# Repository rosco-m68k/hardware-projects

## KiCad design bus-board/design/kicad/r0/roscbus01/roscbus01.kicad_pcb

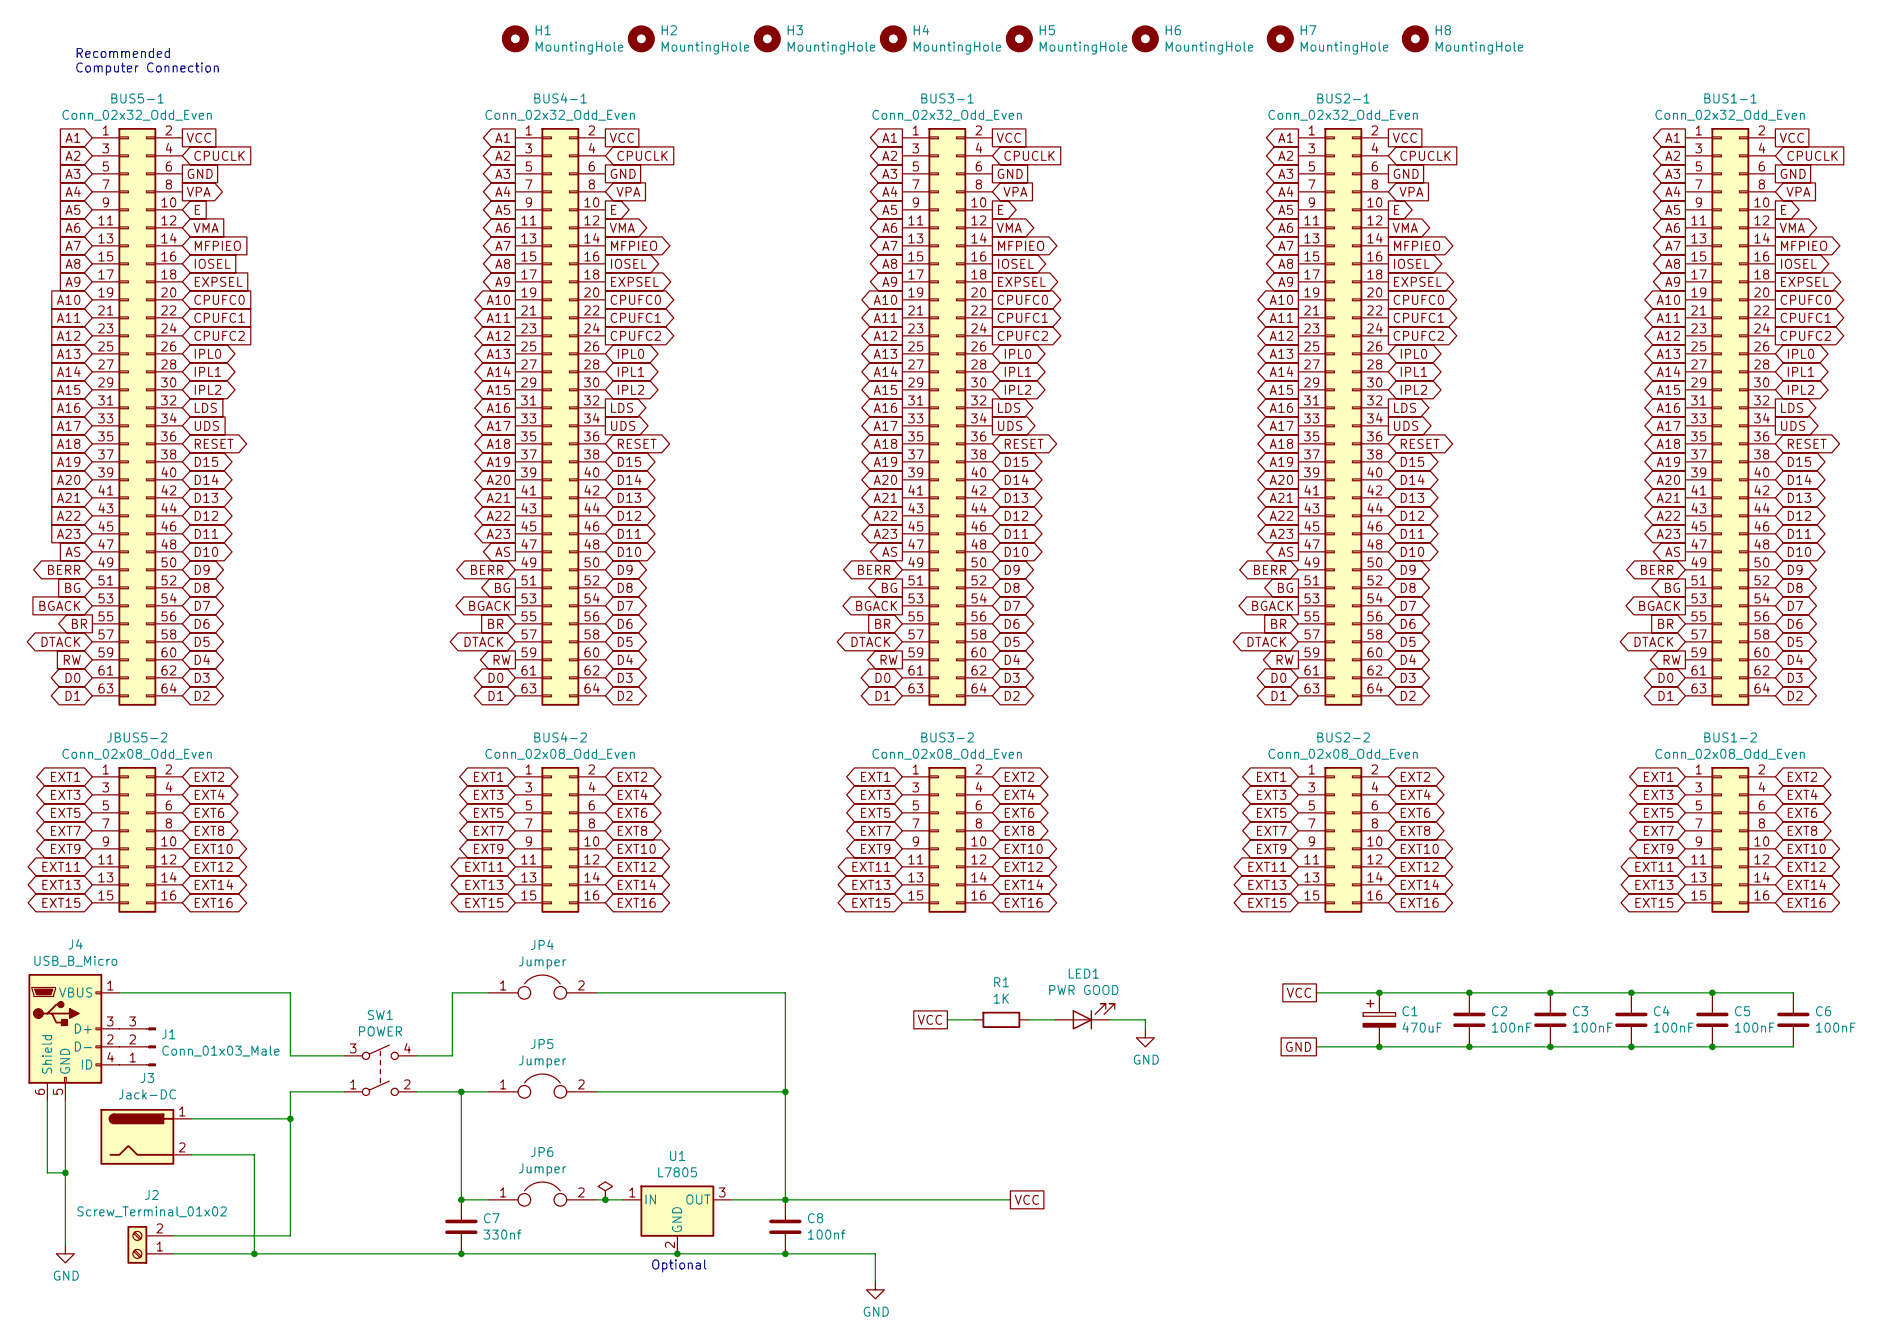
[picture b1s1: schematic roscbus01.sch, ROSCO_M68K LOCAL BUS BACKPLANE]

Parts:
BUS1-1, BUS2-1, BUS3-1, BUS4-1, BUS5-1: Conn_02x32_Odd_Even; pin-2X32
BUS1-2, BUS2-2, BUS3-2, BUS4-2: Conn_02x08_Odd_Even; pin-2X8
C1: 470uF; C-Electrolytic-3,5-10
C2, C3, C4, C5, C6: 100nF; C_Rect_L7.0mm_W2.0mm_P5.00mm
C7: 330nf; C_Rect_L7.0mm_W2.0mm_P5.00mm
C8: 100nf; C_Rect_L7.0mm_W2.0mm_P5.00mm
H1, H2, H3, H4, H5, H6, H7, H8: MountingHole; MountingHole_3.2mm_M3
J1: Conn_01x03_Male; PinHeader_1x03_P2.54mm_Vertical
J2: Screw_Terminal_01x02; TerminalBlock_Phoenix_MPT-0,5-2-2.54_1x02_P2.54mm_Horizontal
J3: Jack-DC; BarrelJack_Wuerth_6941xx301002
J4: USB_B_Micro; USB_Micro-B_Wuerth_614105150721_Vertical
JBUS5-2: Conn_02x08_Odd_Even; pin-2X8
JP4, JP5, JP6: Jumper; PinHeader_1x02_P2.54mm_Vertical
LED1: PWR GOOD; LED_D5.0mm
R1: 1K; R-0207_10
SW1: POWER; NKK-M2021SS1W01
U1: L7805; TO-220F-3_Horizontal_TabDown

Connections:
A1: BUS1-1.1, BUS2-1.1, BUS3-1.1, BUS4-1.1, BUS5-1.1
A2: BUS1-1.3, BUS2-1.3, BUS3-1.3, BUS4-1.3, BUS5-1.3
A3: BUS1-1.5, BUS2-1.5, BUS3-1.5, BUS4-1.5, BUS5-1.5
A4: BUS1-1.7, BUS2-1.7, BUS3-1.7, BUS4-1.7, BUS5-1.7
A5: BUS1-1.9, BUS2-1.9, BUS3-1.9, BUS4-1.9, BUS5-1.9
A6: BUS1-1.11, BUS2-1.11, BUS3-1.11, BUS4-1.11, BUS5-1.11
A7: BUS1-1.13, BUS2-1.13, BUS3-1.13, BUS4-1.13, BUS5-1.13
A8: BUS1-1.15, BUS2-1.15, BUS3-1.15, BUS4-1.15, BUS5-1.15
A9: BUS1-1.17, BUS2-1.17, BUS3-1.17, BUS4-1.17, BUS5-1.17
A10: BUS1-1.19, BUS2-1.19, BUS3-1.19, BUS4-1.19, BUS5-1.19
A11: BUS1-1.21, BUS2-1.21, BUS3-1.21, BUS4-1.21, BUS5-1.21
A12: BUS1-1.23, BUS2-1.23, BUS3-1.23, BUS4-1.23, BUS5-1.23
A13: BUS1-1.25, BUS2-1.25, BUS3-1.25, BUS4-1.25, BUS5-1.25
A14: BUS1-1.27, BUS2-1.27, BUS3-1.27, BUS4-1.27, BUS5-1.27
A15: BUS1-1.29, BUS2-1.29, BUS3-1.29, BUS4-1.29, BUS5-1.29
A16: BUS1-1.31, BUS2-1.31, BUS3-1.31, BUS4-1.31, BUS5-1.31
A17: BUS1-1.33, BUS2-1.33, BUS3-1.33, BUS4-1.33, BUS5-1.33
A18: BUS1-1.35, BUS2-1.35, BUS3-1.35, BUS4-1.35, BUS5-1.35
A19: BUS1-1.37, BUS2-1.37, BUS3-1.37, BUS4-1.37, BUS5-1.37
A20: BUS1-1.39, BUS2-1.39, BUS3-1.39, BUS4-1.39, BUS5-1.39
A21: BUS1-1.41, BUS2-1.41, BUS3-1.41, BUS4-1.41, BUS5-1.41
A22: BUS1-1.43, BUS2-1.43, BUS3-1.43, BUS4-1.43, BUS5-1.43
A23: BUS1-1.45, BUS2-1.45, BUS3-1.45, BUS4-1.45, BUS5-1.45
AS: BUS1-1.47, BUS2-1.47, BUS3-1.47, BUS4-1.47, BUS5-1.47
BERR: BUS1-1.49, BUS2-1.49, BUS3-1.49, BUS4-1.49, BUS5-1.49
BG: BUS1-1.51, BUS2-1.51, BUS3-1.51, BUS4-1.51, BUS5-1.51
BGACK: BUS1-1.53, BUS2-1.53, BUS3-1.53, BUS4-1.53, BUS5-1.53
BR: BUS1-1.55, BUS2-1.55, BUS3-1.55, BUS4-1.55, BUS5-1.55
CPUCLK: BUS1-1.4, BUS2-1.4, BUS3-1.4, BUS4-1.4, BUS5-1.4
CPUFC0: BUS1-1.20, BUS2-1.20, BUS3-1.20, BUS4-1.20, BUS5-1.20
CPUFC1: BUS1-1.22, BUS2-1.22, BUS3-1.22, BUS4-1.22, BUS5-1.22
CPUFC2: BUS1-1.24, BUS2-1.24, BUS3-1.24, BUS4-1.24, BUS5-1.24
D0: BUS1-1.61, BUS2-1.61, BUS3-1.61, BUS4-1.61, BUS5-1.61
D1: BUS1-1.63, BUS2-1.63, BUS3-1.63, BUS4-1.63, BUS5-1.63
D2: BUS1-1.64, BUS2-1.64, BUS3-1.64, BUS4-1.64, BUS5-1.64
D3: BUS1-1.62, BUS2-1.62, BUS3-1.62, BUS4-1.62, BUS5-1.62
D4: BUS1-1.60, BUS2-1.60, BUS3-1.60, BUS4-1.60, BUS5-1.60
D5: BUS1-1.58, BUS2-1.58, BUS3-1.58, BUS4-1.58, BUS5-1.58
D6: BUS1-1.56, BUS2-1.56, BUS3-1.56, BUS4-1.56, BUS5-1.56
D7: BUS1-1.54, BUS2-1.54, BUS3-1.54, BUS4-1.54, BUS5-1.54
D8: BUS1-1.52, BUS2-1.52, BUS3-1.52, BUS4-1.52, BUS5-1.52
D9: BUS1-1.50, BUS2-1.50, BUS3-1.50, BUS4-1.50, BUS5-1.50
D10: BUS1-1.48, BUS2-1.48, BUS3-1.48, BUS4-1.48, BUS5-1.48
D11: BUS1-1.46, BUS2-1.46, BUS3-1.46, BUS4-1.46, BUS5-1.46
D12: BUS1-1.44, BUS2-1.44, BUS3-1.44, BUS4-1.44, BUS5-1.44
D13: BUS1-1.42, BUS2-1.42, BUS3-1.42, BUS4-1.42, BUS5-1.42
D14: BUS1-1.40, BUS2-1.40, BUS3-1.40, BUS4-1.40, BUS5-1.40
D15: BUS1-1.38, BUS2-1.38, BUS3-1.38, BUS4-1.38, BUS5-1.38
DTACK: BUS1-1.57, BUS2-1.57, BUS3-1.57, BUS4-1.57, BUS5-1.57
E: BUS1-1.10, BUS2-1.10, BUS3-1.10, BUS4-1.10, BUS5-1.10
EXPSEL: BUS1-1.18, BUS2-1.18, BUS3-1.18, BUS4-1.18, BUS5-1.18
EXT1: BUS1-2.1, BUS2-2.1, BUS3-2.1, BUS4-2.1, JBUS5-2.1
EXT2: BUS1-2.2, BUS2-2.2, BUS3-2.2, BUS4-2.2, JBUS5-2.2
EXT3: BUS1-2.3, BUS2-2.3, BUS3-2.3, BUS4-2.3, JBUS5-2.3
EXT4: BUS1-2.4, BUS2-2.4, BUS3-2.4, BUS4-2.4, JBUS5-2.4
EXT5: BUS1-2.5, BUS2-2.5, BUS3-2.5, BUS4-2.5, JBUS5-2.5
EXT6: BUS1-2.6, BUS2-2.6, BUS3-2.6, BUS4-2.6, JBUS5-2.6
EXT7: BUS1-2.7, BUS2-2.7, BUS3-2.7, BUS4-2.7, JBUS5-2.7
EXT8: BUS1-2.8, BUS2-2.8, BUS3-2.8, BUS4-2.8, JBUS5-2.8
EXT9: BUS1-2.9, BUS2-2.9, BUS3-2.9, BUS4-2.9, JBUS5-2.9
EXT10: BUS1-2.10, BUS2-2.10, BUS3-2.10, BUS4-2.10, JBUS5-2.10
EXT11: BUS1-2.11, BUS2-2.11, BUS3-2.11, BUS4-2.11, JBUS5-2.11
EXT12: BUS1-2.12, BUS2-2.12, BUS3-2.12, BUS4-2.12, JBUS5-2.12
EXT13: BUS1-2.13, BUS2-2.13, BUS3-2.13, BUS4-2.13, JBUS5-2.13
EXT14: BUS1-2.14, BUS2-2.14, BUS3-2.14, BUS4-2.14, JBUS5-2.14
EXT15: BUS1-2.15, BUS2-2.15, BUS3-2.15, BUS4-2.15, JBUS5-2.15
EXT16: BUS1-2.16, BUS2-2.16, BUS3-2.16, BUS4-2.16, JBUS5-2.16
GND: BUS1-1.6, BUS2-1.6, BUS3-1.6, BUS4-1.6, BUS5-1.6, C1.2, C2.2, C3.2, C4.2, C5.2, C6.2, C7.2, C8.2, J2.1, J3.2, J4.5 (GND), J4.6 (Shield), LED1.1 (K), U1.2 (GND)
IOSEL: BUS1-1.16, BUS2-1.16, BUS3-1.16, BUS4-1.16, BUS5-1.16
IPL0: BUS1-1.26, BUS2-1.26, BUS3-1.26, BUS4-1.26, BUS5-1.26
IPL1: BUS1-1.28, BUS2-1.28, BUS3-1.28, BUS4-1.28, BUS5-1.28
IPL2: BUS1-1.30, BUS2-1.30, BUS3-1.30, BUS4-1.30, BUS5-1.30
LDS: BUS1-1.32, BUS2-1.32, BUS3-1.32, BUS4-1.32, BUS5-1.32
MFPIEO: BUS1-1.14, BUS2-1.14, BUS3-1.14, BUS4-1.14, BUS5-1.14
unnamed: C7.1, JP5.1, JP6.1, SW1.2
unnamed: J1.1, J4.4 (ID)
unnamed: J1.2, J4.2 (D-)
unnamed: J1.3, J4.3 (D+)
unnamed: J2.2, J3.1, SW1.1
unnamed: J4.1 (VBUS), SW1.3
unnamed: JP4.1, SW1.4
unnamed: JP6.2, U1.1 (IN)
unnamed: LED1.2 (A), R1.1
RESET: BUS1-1.36, BUS2-1.36, BUS3-1.36, BUS4-1.36, BUS5-1.36
RW: BUS1-1.59, BUS2-1.59, BUS3-1.59, BUS4-1.59, BUS5-1.59
UDS: BUS1-1.34, BUS2-1.34, BUS3-1.34, BUS4-1.34, BUS5-1.34
VCC: BUS1-1.2, BUS2-1.2, BUS3-1.2, BUS4-1.2, BUS5-1.2, C1.1, C2.1, C3.1, C4.1, C5.1, C6.1, C8.1, JP4.2, JP5.2, R1.2, U1.3 (OUT)
VMA: BUS1-1.12, BUS2-1.12, BUS3-1.12, BUS4-1.12, BUS5-1.12
VPA: BUS1-1.8, BUS2-1.8, BUS3-1.8, BUS4-1.8, BUS5-1.8

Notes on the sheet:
Recommended Computer Connection
Optional

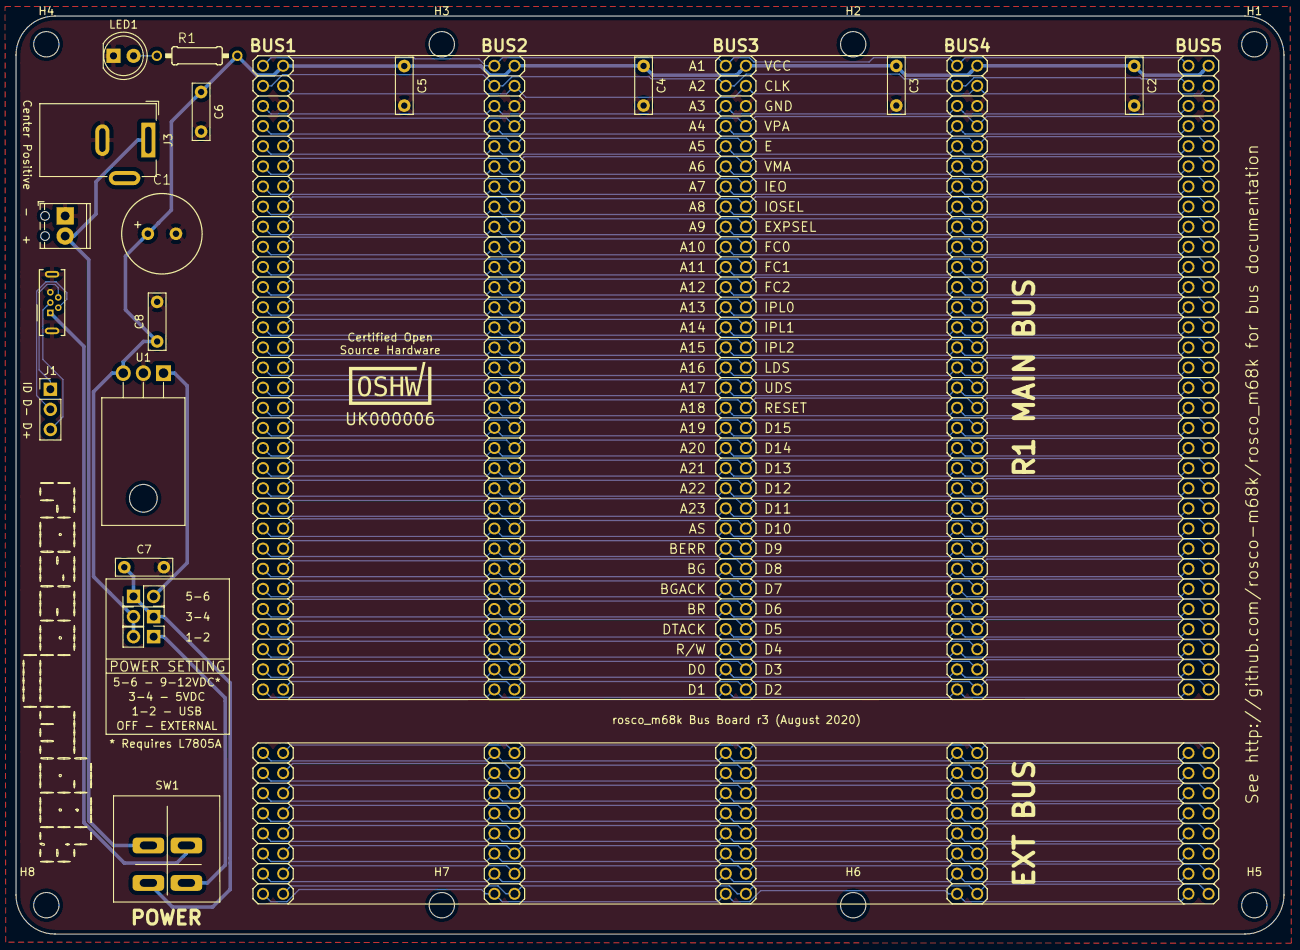
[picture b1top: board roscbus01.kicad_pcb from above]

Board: 2 copper layers, 160.1 x 115.9 mm, 38 parts (0 on the bottom side), 89 nets.

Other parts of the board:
OSHW_Mono_0.25_Scale: UK000006; OSHW_Mono_0.25_Scale

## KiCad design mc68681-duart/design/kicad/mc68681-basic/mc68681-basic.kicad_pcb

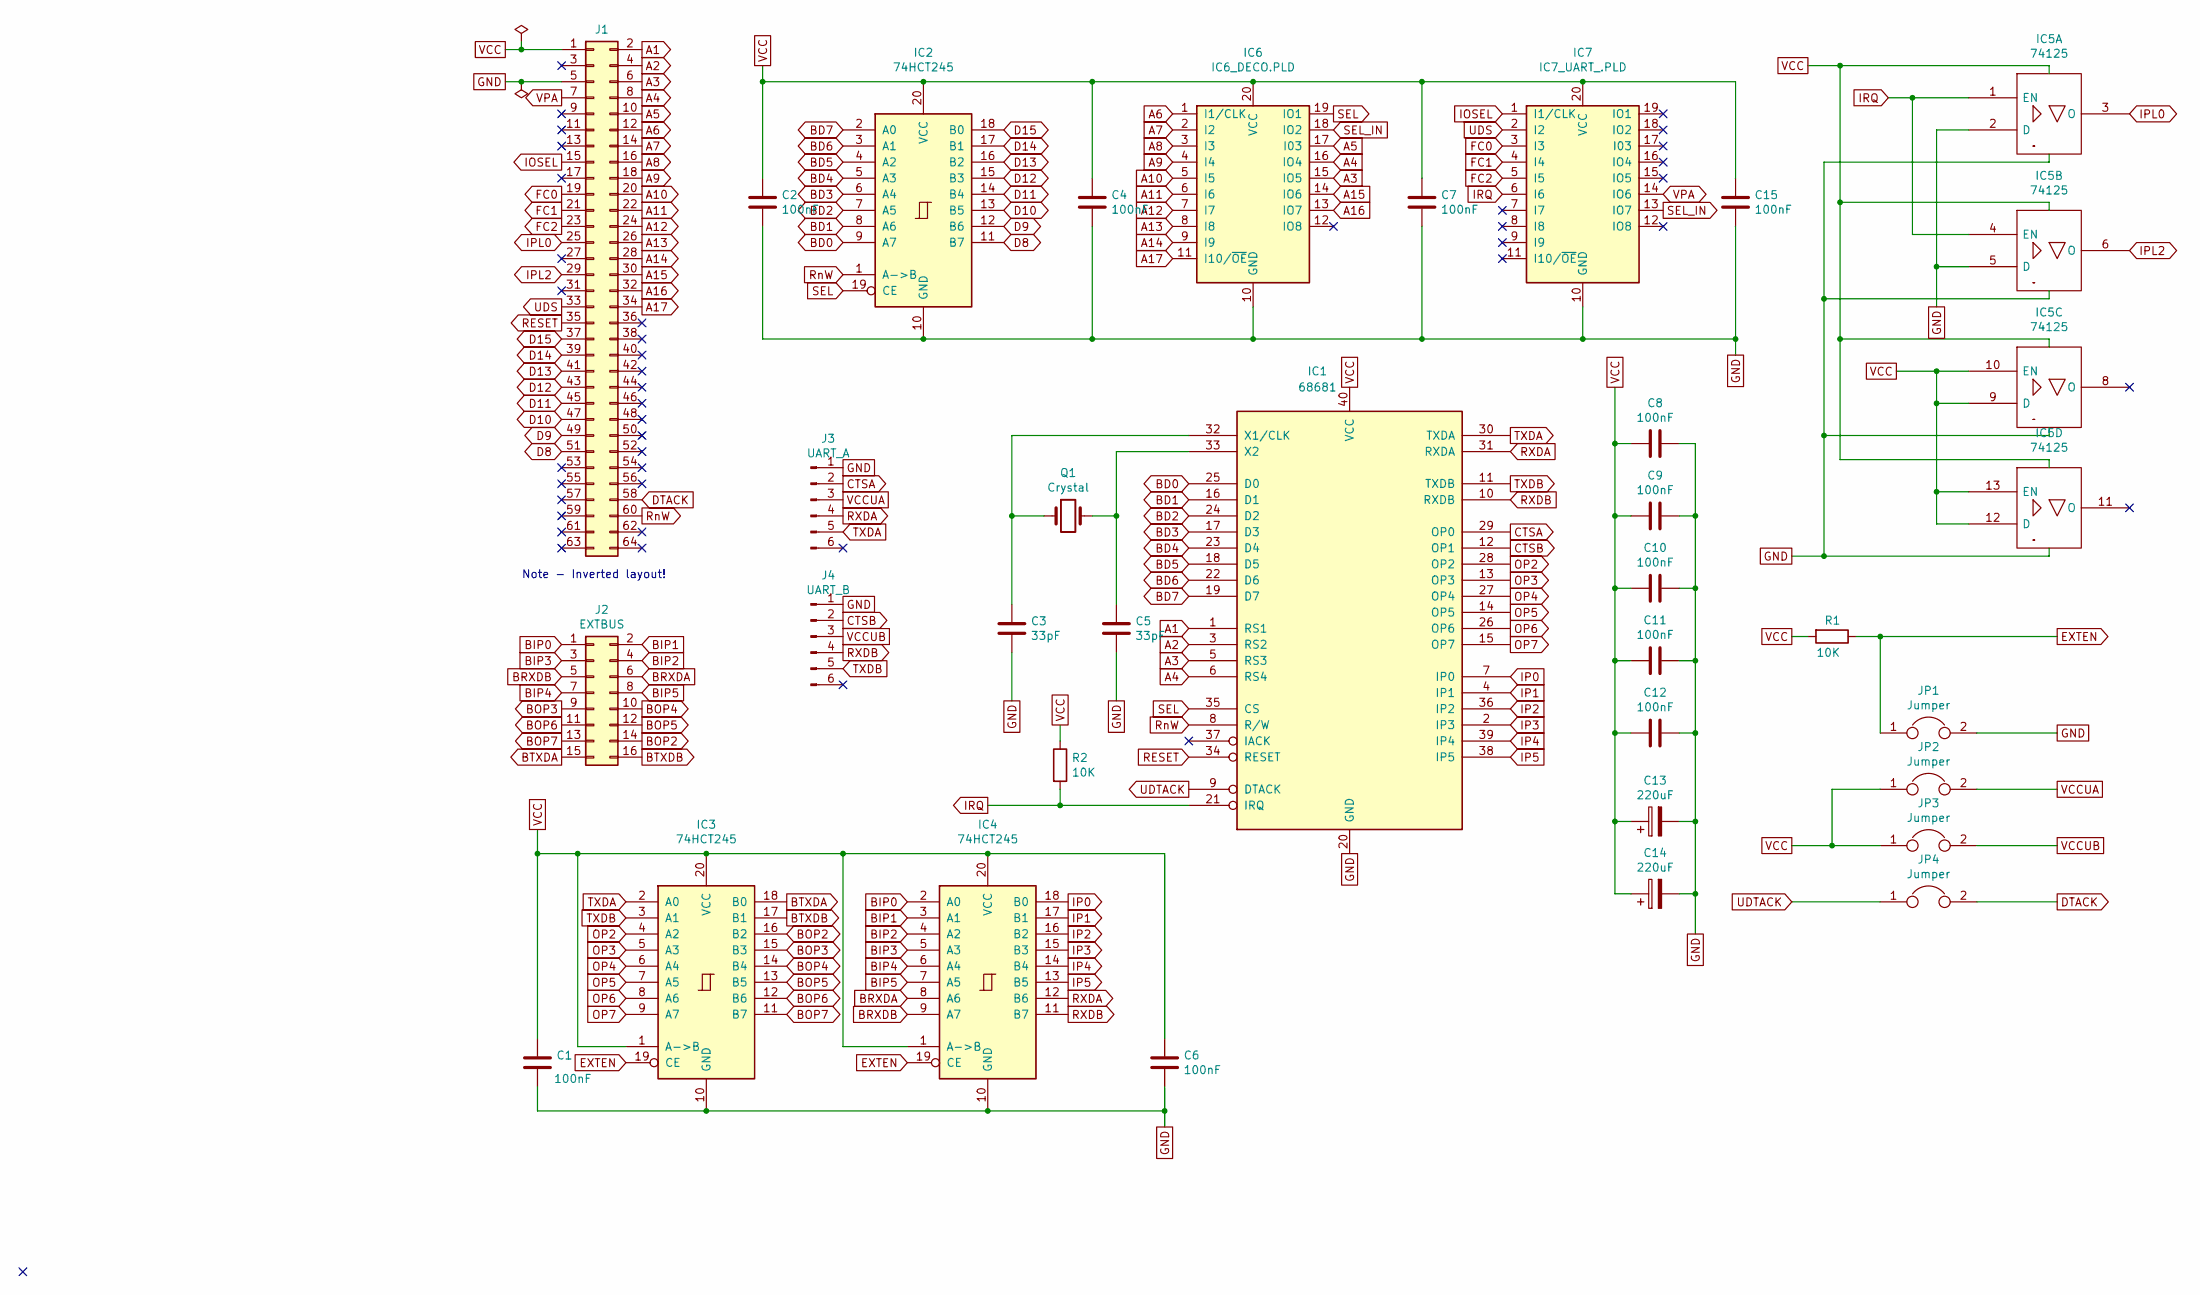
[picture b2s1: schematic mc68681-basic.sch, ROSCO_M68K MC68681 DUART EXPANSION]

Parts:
C1, C2, C4, C6, C7, C8, C9, C10, C11, C12, C15: 100nF; C2.5-3
C3, C5: 33pF; C2.5-3
C13, C14: 220uF; CP_Radial_D6.3mm_P2.50mm
IC1: 68681; DIP-40_W15.24mm_Socket_LongPads
IC2, IC3, IC4: 74HCT245; DIP-20_W7.62mm_Socket_LongPads
IC5: 74125; DIP-14_W7.62mm_Socket_LongPads
IC6: IC6_DECO.PLD; DIP-20_W7.62mm_Socket_LongPads
IC7: IC7_UART_.PLD; DIP-20_W7.62mm_Socket_LongPads
J1: Conn_02x32_Odd_Even; PinHeader_2x32_P2.54mm_Vertical
J2: EXTBUS; PinHeader_2x08_P2.54mm_Vertical
J3: UART_A; PinHeader_1x06_P2.54mm_Vertical
J4: UART_B; PinHeader_1x06_P2.54mm_Vertical
JP1, JP2, JP3, JP4: Jumper; PinHeader_1x02_P2.54mm_Vertical
Q1: Crystal; Crystal_HC49-4H_Vertical
R1, R2: 10K; R_Axial_DIN0207_L6.3mm_D2.5mm_P10.16mm_Horizontal

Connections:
A1: IC1.1 (RS1), J1.2
A2: IC1.3 (RS2), J1.4
A3: IC1.5 (RS3), IC6.15 (IO5), J1.6
A4: IC1.6 (RS4), IC6.16 (IO4), J1.8
A5: IC6.17 (I03), J1.10
A6: IC6.1 (I1/CLK), J1.12
A7: IC6.2 (I2), J1.14
A8: IC6.3 (I3), J1.16
A9: IC6.4 (I4), J1.18
A10: IC6.5 (I5), J1.20
A11: IC6.6 (I6), J1.22
A12: IC6.7 (I7), J1.24
A13: IC6.8 (I8), J1.26
A14: IC6.9 (I9), J1.28
A15: IC6.14 (IO6), J1.30
A16: IC6.13 (IO7), J1.32
A17: IC6.11 (I10/~OE~), J1.34
BD0: IC1.25 (D0), IC2.9 (A7)
BD1: IC1.16 (D1), IC2.8 (A6)
BD2: IC1.24 (D2), IC2.7 (A5)
BD3: IC1.17 (D3), IC2.6 (A4)
BD4: IC1.23 (D4), IC2.5 (A3)
BD5: IC1.18 (D5), IC2.4 (A2)
BD6: IC1.22 (D6), IC2.3 (A1)
BD7: IC1.19 (D7), IC2.2 (A0)
BIP0: IC4.2 (A0), J2.1
BIP1: IC4.3 (A1), J2.2
BIP2: IC4.4 (A2), J2.4
BIP3: IC4.5 (A3), J2.3
BIP4: IC4.6 (A4), J2.7
BIP5: IC4.7 (A5), J2.8
BOP2: IC3.16 (B2), J2.14
BOP3: IC3.15 (B3), J2.9
BOP4: IC3.14 (B4), J2.10
BOP5: IC3.13 (B5), J2.12
BOP6: IC3.12 (B6), J2.11
BOP7: IC3.11 (B7), J2.13
BRXDA: IC4.8 (A6), J2.6
BRXDB: IC4.9 (A7), J2.5
BTXDA: IC3.18 (B0), J2.15
BTXDB: IC3.17 (B1), J2.16
CTSA: IC1.29 (OP0), J3.2
CTSB: IC1.12 (OP1), J4.2
D8: IC2.11 (B7), J1.51
D9: IC2.12 (B6), J1.49
D10: IC2.13 (B5), J1.47
D11: IC2.14 (B4), J1.45
D12: IC2.15 (B3), J1.43
D13: IC2.16 (B2), J1.41
D14: IC2.17 (B1), J1.39
D15: IC2.18 (B0), J1.37
DTACK: J1.58, JP4.2
EXTEN: IC3.19 (CE), IC4.19 (CE), JP1.1, R1.1
FC0: IC7.3 (I3), J1.19
FC1: IC7.4 (I4), J1.21
FC2: IC7.5 (I5), J1.23
IOSEL: IC7.1 (I1/CLK), J1.15
IP0: IC1.7 (IP0), IC4.18 (B0)
IP1: IC1.4 (IP1), IC4.17 (B1)
IP2: IC1.36 (IP2), IC4.16 (B2)
IP3: IC1.2 (IP3), IC4.15 (B3)
IP4: IC1.39 (IP4), IC4.14 (B4)
IP5: IC1.38 (IP5), IC4.13 (B5)
IPL0: IC5.3 (O), J1.25
IPL2: IC5.6 (O), J1.29
IRQ: IC1.21 (IRQ), IC5.1 (EN), IC5.4 (EN), IC7.6 (I6), R2.2
unnamed: C3.1, IC1.32 (X1/CLK), Q1.1
unnamed: C5.1, IC1.33 (X2), Q1.2
OP2: IC1.28 (OP2), IC3.4 (A2)
OP3: IC1.13 (OP3), IC3.5 (A3)
OP4: IC1.27 (OP4), IC3.6 (A4)
OP5: IC1.14 (OP5), IC3.7 (A5)
OP6: IC1.26 (OP6), IC3.8 (A6)
OP7: IC1.15 (OP7), IC3.9 (A7)
RESET: IC1.34 (RESET), J1.35
RXDA: IC1.31 (RXDA), IC4.12 (B6), J3.4
RXDB: IC1.10 (RXDB), IC4.11 (B7), J4.4
RnW: IC1.8 (R/W), IC2.1 (A->B), J1.60
SEL: IC1.35 (CS), IC2.19 (CE), IC6.19 (IO1)
SEL_IN: IC6.18 (IO2), IC7.13 (IO7)
TXDA: IC1.30 (TXDA), IC3.2 (A0), J3.5
TXDB: IC1.11 (TXDB), IC3.3 (A1), J4.5
UDS: IC7.2 (I2), J1.33
UDTACK: IC1.9 (DTACK), JP4.1
VCCUA: J3.3, JP2.2
VCCUB: J4.3, JP3.2
VPA: IC7.14 (IO6), J1.7

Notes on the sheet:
Note - Inverted layout!

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
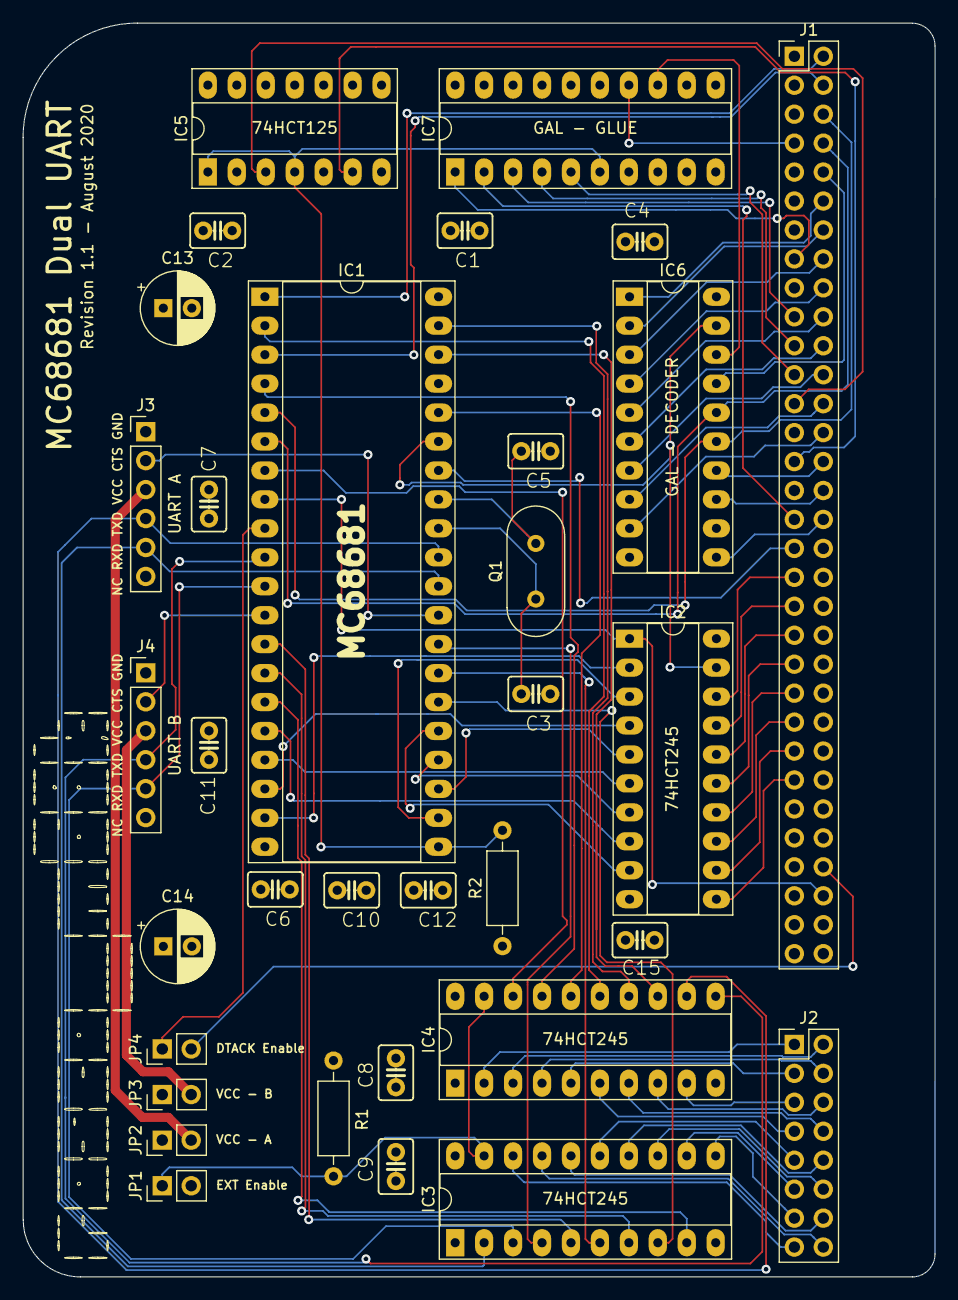
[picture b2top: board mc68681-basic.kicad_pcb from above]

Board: 4 copper layers, 80.0 x 110.0 mm, 33 parts (0 on the bottom side), 89 nets.

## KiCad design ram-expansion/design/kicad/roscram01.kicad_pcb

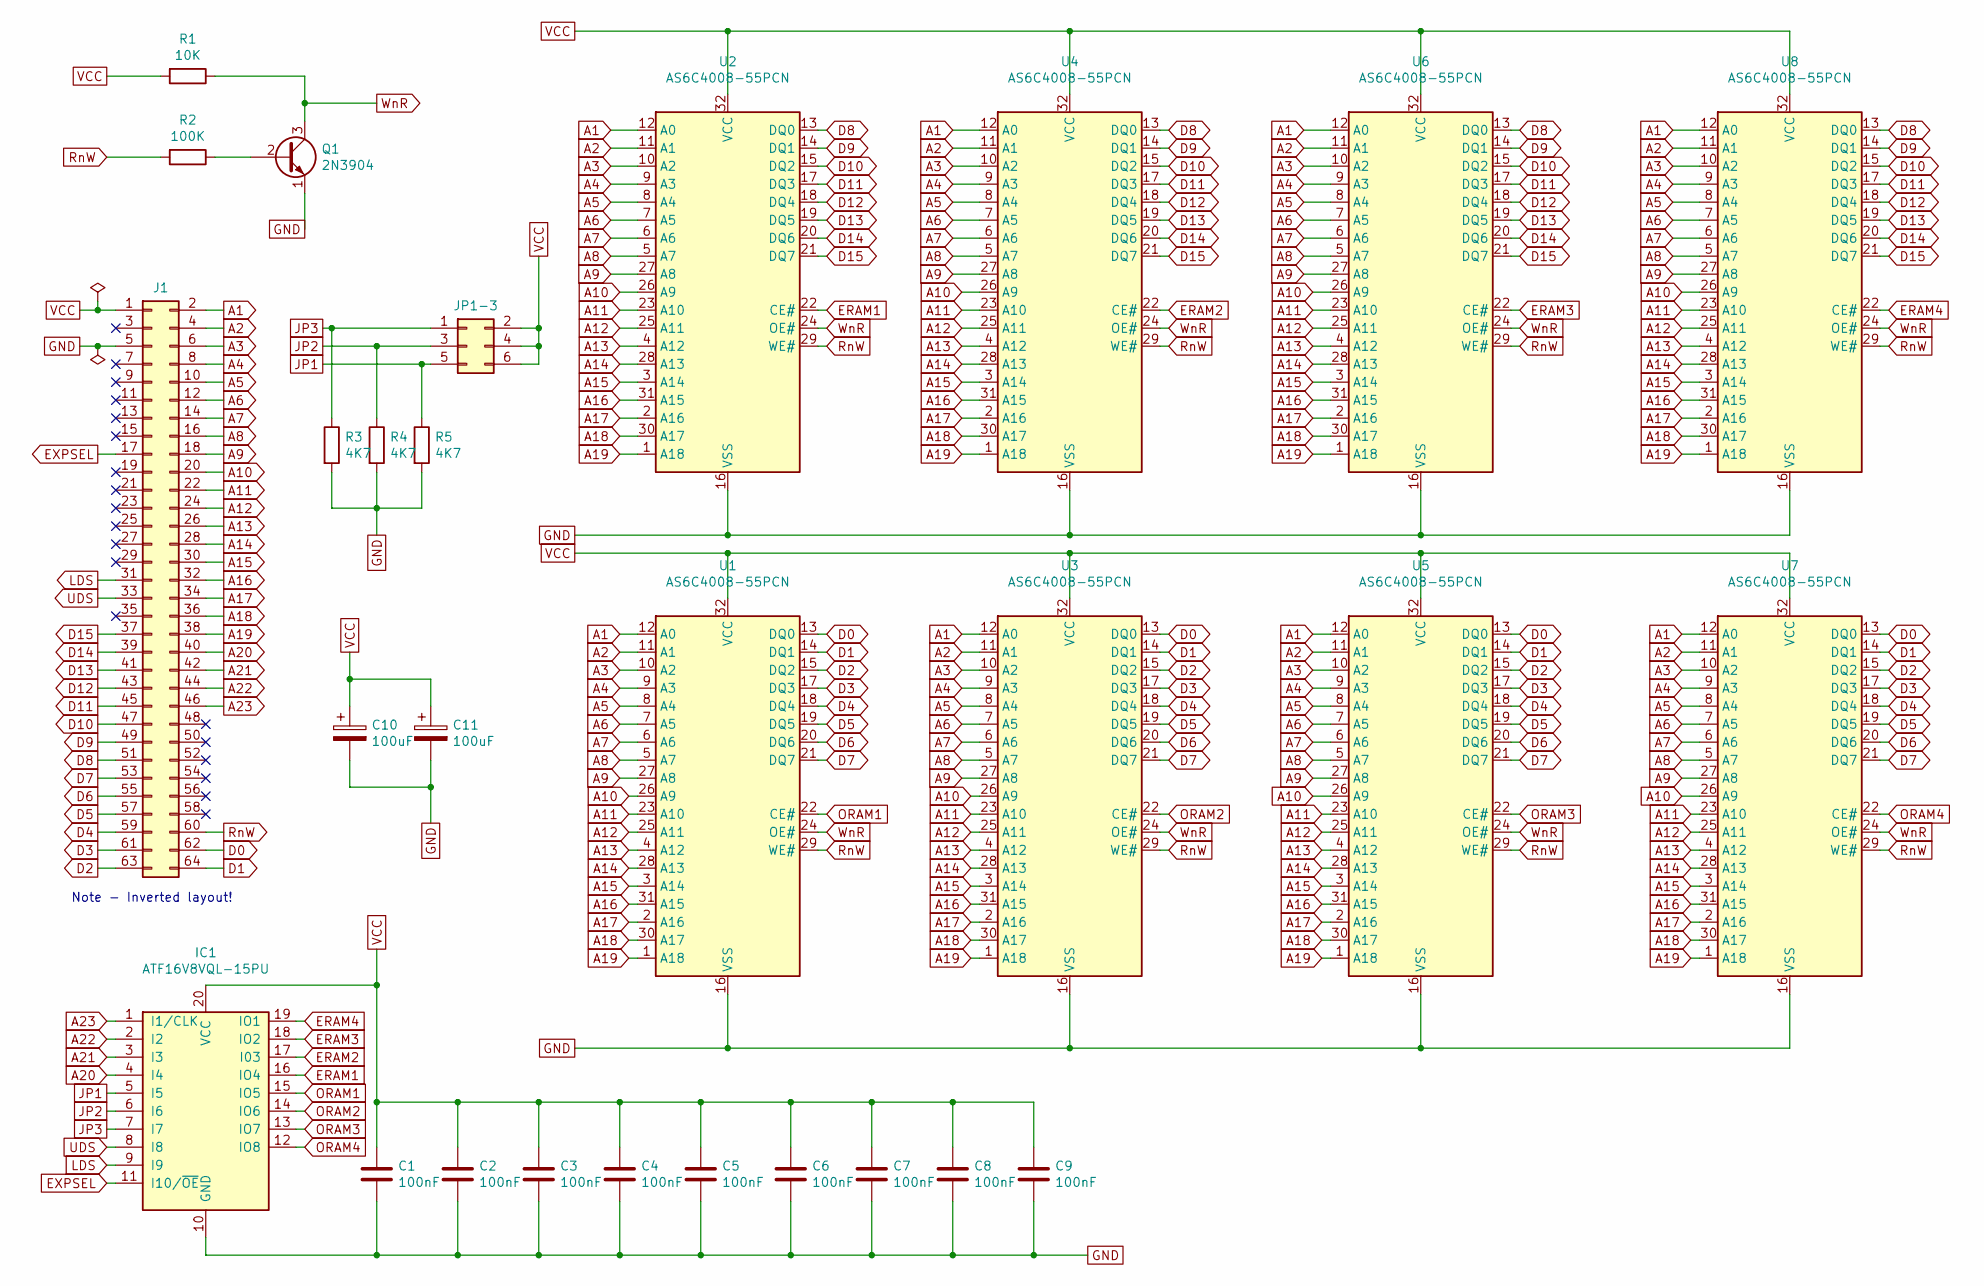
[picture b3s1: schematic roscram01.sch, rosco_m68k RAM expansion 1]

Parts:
C1, C2, C3, C4, C5, C6, C7, C8, C9: 100nF; C2.5-3
C10, C11: 100uF; C-Electolytic-2,5-5
IC1: ATF16V8VQL-15PU; DIL20
J1: Conn_02x32_Odd_Even; pin-2X32
JP1-3: Conn_02x03_Odd_Even; pin-2X3
Q1: 2N3904; TO-92_Inline
R1: 10K; R-0207_10
R2: 100K; R-0207_10
R3, R4, R5: 4K7; R-0207_10
U1, U2, U3, U4, U5, U6, U7, U8: AS6C4008-55PCN; DIP-32_W15.24mm

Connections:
A1: J1.2, U1.12 (A0), U2.12 (A0), U3.12 (A0), U4.12 (A0), U5.12 (A0), U6.12 (A0), U7.12 (A0), U8.12 (A0)
A2: J1.4, U1.11 (A1), U2.11 (A1), U3.11 (A1), U4.11 (A1), U5.11 (A1), U6.11 (A1), U7.11 (A1), U8.11 (A1)
A3: J1.6, U1.10 (A2), U2.10 (A2), U3.10 (A2), U4.10 (A2), U5.10 (A2), U6.10 (A2), U7.10 (A2), U8.10 (A2)
A4: J1.8, U1.9 (A3), U2.9 (A3), U3.9 (A3), U4.9 (A3), U5.9 (A3), U6.9 (A3), U7.9 (A3), U8.9 (A3)
A5: J1.10, U1.8 (A4), U2.8 (A4), U3.8 (A4), U4.8 (A4), U5.8 (A4), U6.8 (A4), U7.8 (A4), U8.8 (A4)
A6: J1.12, U1.7 (A5), U2.7 (A5), U3.7 (A5), U4.7 (A5), U5.7 (A5), U6.7 (A5), U7.7 (A5), U8.7 (A5)
A7: J1.14, U1.6 (A6), U2.6 (A6), U3.6 (A6), U4.6 (A6), U5.6 (A6), U6.6 (A6), U7.6 (A6), U8.6 (A6)
A8: J1.16, U1.5 (A7), U2.5 (A7), U3.5 (A7), U4.5 (A7), U5.5 (A7), U6.5 (A7), U7.5 (A7), U8.5 (A7)
A9: J1.18, U1.27 (A8), U2.27 (A8), U3.27 (A8), U4.27 (A8), U5.27 (A8), U6.27 (A8), U7.27 (A8), U8.27 (A8)
A10: J1.20, U1.26 (A9), U2.26 (A9), U3.26 (A9), U4.26 (A9), U5.26 (A9), U6.26 (A9), U7.26 (A9), U8.26 (A9)
A11: J1.22, U1.23 (A10), U2.23 (A10), U3.23 (A10), U4.23 (A10), U5.23 (A10), U6.23 (A10), U7.23 (A10), U8.23 (A10)
A12: J1.24, U1.25 (A11), U2.25 (A11), U3.25 (A11), U4.25 (A11), U5.25 (A11), U6.25 (A11), U7.25 (A11), U8.25 (A11)
A13: J1.26, U1.4 (A12), U2.4 (A12), U3.4 (A12), U4.4 (A12), U5.4 (A12), U6.4 (A12), U7.4 (A12), U8.4 (A12)
A14: J1.28, U1.28 (A13), U2.28 (A13), U3.28 (A13), U4.28 (A13), U5.28 (A13), U6.28 (A13), U7.28 (A13), U8.28 (A13)
A15: J1.30, U1.3 (A14), U2.3 (A14), U3.3 (A14), U4.3 (A14), U5.3 (A14), U6.3 (A14), U7.3 (A14), U8.3 (A14)
A16: J1.32, U1.31 (A15), U2.31 (A15), U3.31 (A15), U4.31 (A15), U5.31 (A15), U6.31 (A15), U7.31 (A15), U8.31 (A15)
A17: J1.34, U1.2 (A16), U2.2 (A16), U3.2 (A16), U4.2 (A16), U5.2 (A16), U6.2 (A16), U7.2 (A16), U8.2 (A16)
A18: J1.36, U1.30 (A17), U2.30 (A17), U3.30 (A17), U4.30 (A17), U5.30 (A17), U6.30 (A17), U7.30 (A17), U8.30 (A17)
A19: J1.38, U1.1 (A18), U2.1 (A18), U3.1 (A18), U4.1 (A18), U5.1 (A18), U6.1 (A18), U7.1 (A18), U8.1 (A18)
A20: IC1.4 (I4), J1.40
A21: IC1.3 (I3), J1.42
A22: IC1.2 (I2), J1.44
A23: IC1.1 (I1/CLK), J1.46
D0: J1.62, U1.13 (DQ0), U3.13 (DQ0), U5.13 (DQ0), U7.13 (DQ0)
D1: J1.64, U1.14 (DQ1), U3.14 (DQ1), U5.14 (DQ1), U7.14 (DQ1)
D2: J1.63, U1.15 (DQ2), U3.15 (DQ2), U5.15 (DQ2), U7.15 (DQ2)
D3: J1.61, U1.17 (DQ3), U3.17 (DQ3), U5.17 (DQ3), U7.17 (DQ3)
D4: J1.59, U1.18 (DQ4), U3.18 (DQ4), U5.18 (DQ4), U7.18 (DQ4)
D5: J1.57, U1.19 (DQ5), U3.19 (DQ5), U5.19 (DQ5), U7.19 (DQ5)
D6: J1.55, U1.20 (DQ6), U3.20 (DQ6), U5.20 (DQ6), U7.20 (DQ6)
D7: J1.53, U1.21 (DQ7), U3.21 (DQ7), U5.21 (DQ7), U7.21 (DQ7)
D8: J1.51, U2.13 (DQ0), U4.13 (DQ0), U6.13 (DQ0), U8.13 (DQ0)
D9: J1.49, U2.14 (DQ1), U4.14 (DQ1), U6.14 (DQ1), U8.14 (DQ1)
D10: J1.47, U2.15 (DQ2), U4.15 (DQ2), U6.15 (DQ2), U8.15 (DQ2)
D11: J1.45, U2.17 (DQ3), U4.17 (DQ3), U6.17 (DQ3), U8.17 (DQ3)
D12: J1.43, U2.18 (DQ4), U4.18 (DQ4), U6.18 (DQ4), U8.18 (DQ4)
D13: J1.41, U2.19 (DQ5), U4.19 (DQ5), U6.19 (DQ5), U8.19 (DQ5)
D14: J1.39, U2.20 (DQ6), U4.20 (DQ6), U6.20 (DQ6), U8.20 (DQ6)
D15: J1.37, U2.21 (DQ7), U4.21 (DQ7), U6.21 (DQ7), U8.21 (DQ7)
ERAM1: IC1.16 (IO4), U2.22 (CE#)
ERAM2: IC1.17 (I03), U4.22 (CE#)
ERAM3: IC1.18 (IO2), U6.22 (CE#)
ERAM4: IC1.19 (IO1), U8.22 (CE#)
EXPSEL: IC1.11 (I10/~OE~), J1.17
JP1: IC1.5 (I5), JP1-3.5, R5.1
JP2: IC1.6 (I6), JP1-3.3, R4.1
JP3: IC1.7 (I7), JP1-3.1, R3.1
LDS: IC1.9 (I9), J1.31
unnamed: Q1.2 (B), R2.1
ORAM1: IC1.15 (IO5), U1.22 (CE#)
ORAM2: IC1.14 (IO6), U3.22 (CE#)
ORAM3: IC1.13 (IO7), U5.22 (CE#)
ORAM4: IC1.12 (IO8), U7.22 (CE#)
RnW: J1.60, R2.2, U1.29 (WE#), U2.29 (WE#), U3.29 (WE#), U4.29 (WE#), U5.29 (WE#), U6.29 (WE#), U7.29 (WE#), U8.29 (WE#)
UDS: IC1.8 (I8), J1.33
WnR: Q1.3 (C), R1.1, U1.24 (OE#), U2.24 (OE#), U3.24 (OE#), U4.24 (OE#), U5.24 (OE#), U6.24 (OE#), U7.24 (OE#), U8.24 (OE#)

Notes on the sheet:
Note - Inverted layout!

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
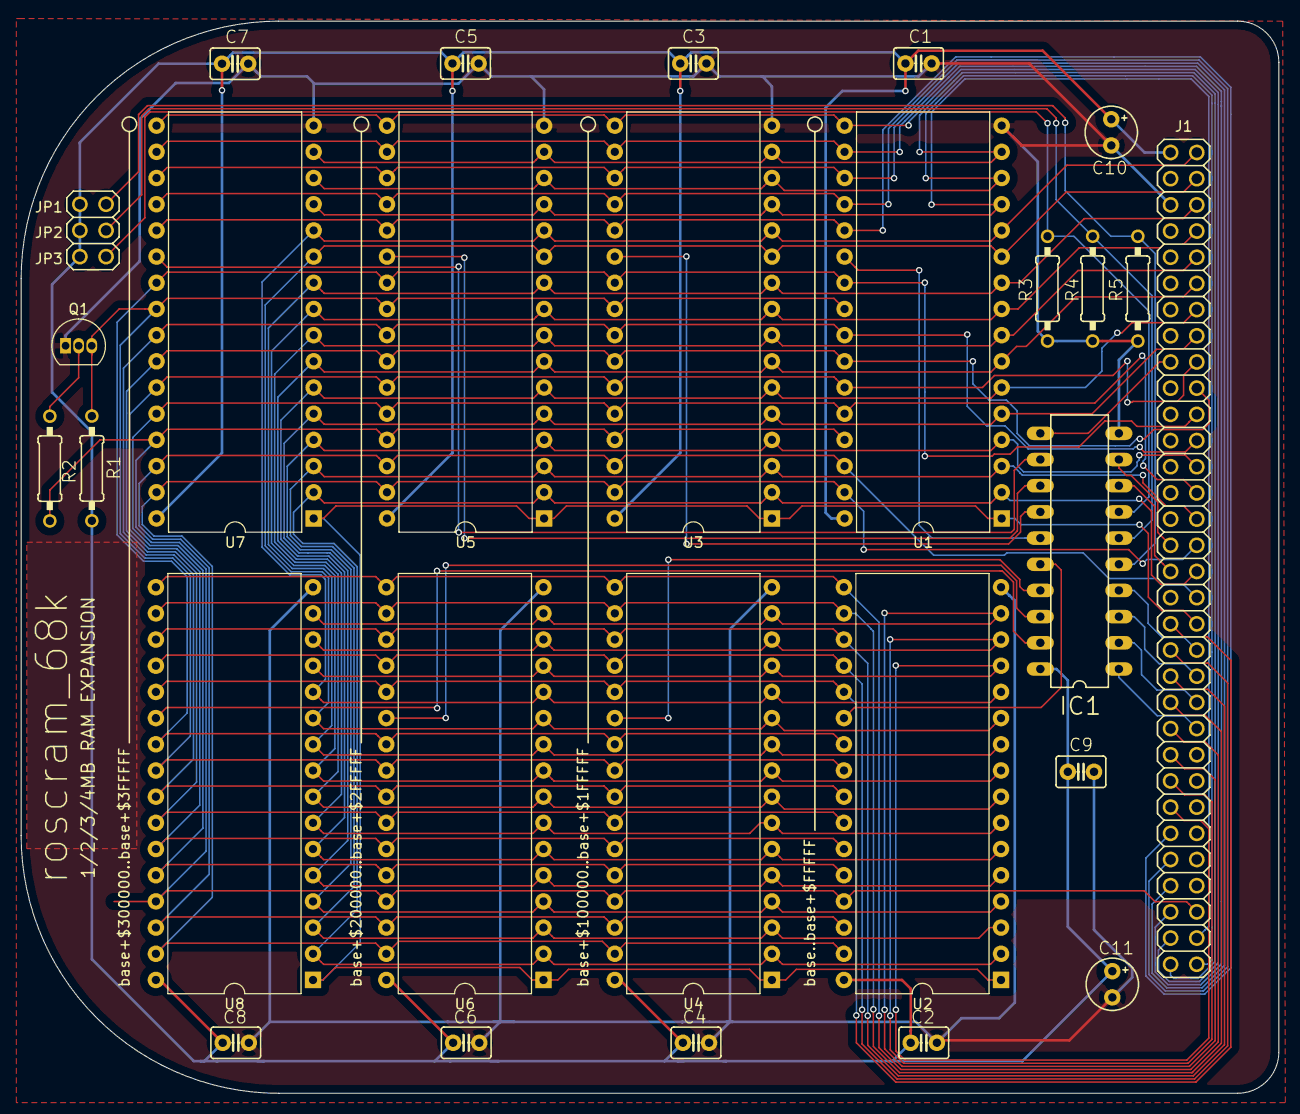
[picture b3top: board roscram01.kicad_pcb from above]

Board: 2 copper layers, 122.0 x 104.0 mm, 28 parts (0 on the bottom side), 58 nets.

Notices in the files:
bus-board/design/kicad/r0/roscbus01/roscbus01.kicad_pcb:
Copyright ©2020 Ross Bamford & Contributors
bus-board/design/kicad/r0/roscbus01/roscbus01.sch:
Open Source Hardware licenced under CERN Open Hardware Licence
Copyright 2020 Ross Bamford and Contributors
mc68681-duart/design/kicad/mc68681-basic/mc68681-basic.sch:
Copyright ©2020 Ross Bamford and Contributors
ram-expansion/design/kicad/roscram01.sch:
Open-Source Hardware licenced under the CERN Open Hardware Licence
